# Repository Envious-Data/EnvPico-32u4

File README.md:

# EnvPico-32u4
Atmega32U4 board in the footprint of a Raspberry pi Pico, primarily inteded to be used for QMK

As you can imagine this is another kicad thing I just threw together on a whim but I did spend a bit more effort on this one and I might actually get this PCB made since I would like to get QMK properly running on my keyboards with VIA support.

Other than that it seems a bit easier to get Atmel chips over STM32s at the moment.

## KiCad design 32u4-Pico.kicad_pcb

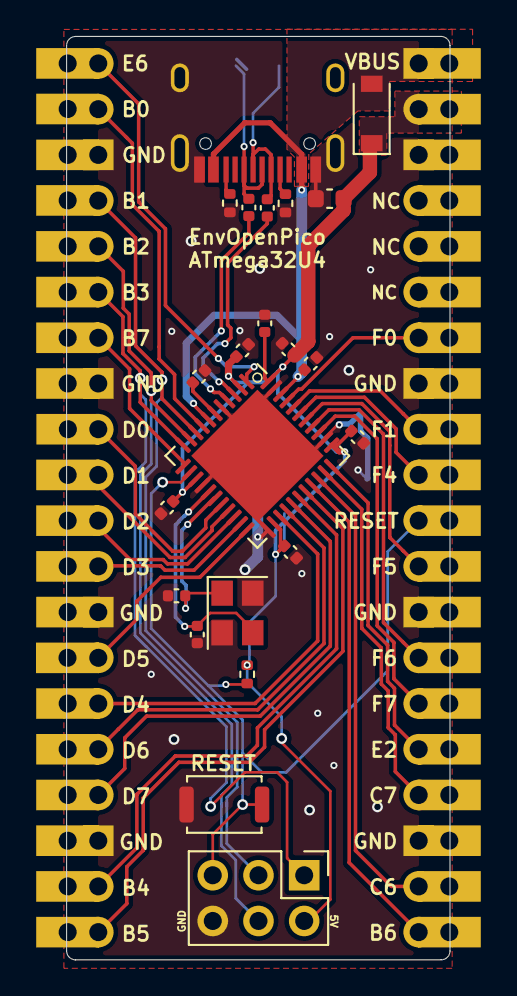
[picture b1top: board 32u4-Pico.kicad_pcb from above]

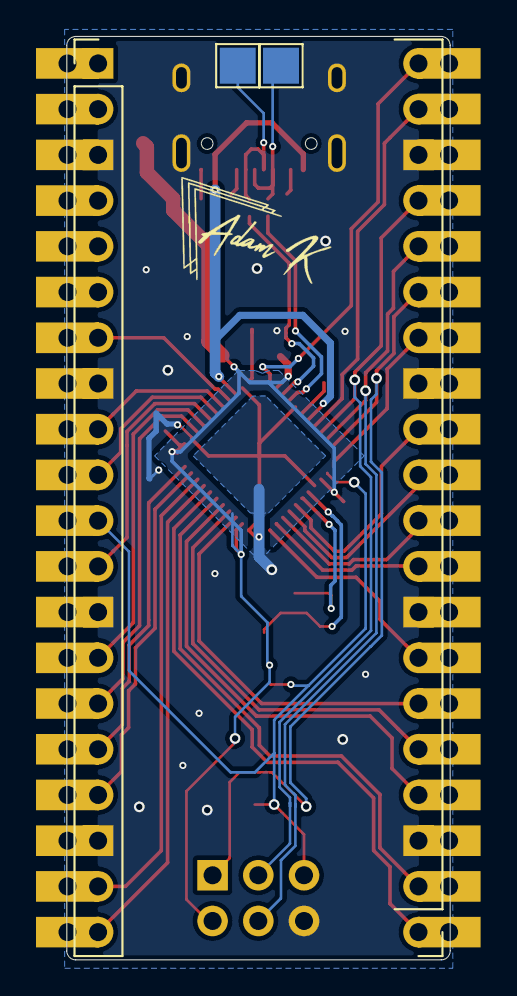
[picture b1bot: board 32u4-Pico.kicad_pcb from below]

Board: 2 copper layers, 21.3 x 51.3 mm, 26 parts (4 on the bottom side), 39 nets.

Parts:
C1: 10uf 0603 6.3V; C_0603_1608Metric
C2, C7: 22pF 0402; C_0402_1005Metric
C3, C10: 1uf 0402; C_0402_1005Metric
C4: 1uF 0402; C_0402_1005Metric
C5, C6, C8, C11, C13: 100nf 0402; C_0402_1005Metric
D1: 1n40002; D_SOD-123
ISP1: AVR-ISP-6; PinHeader_2x03_P2.54mm_Vertical
J3, J4: 2.54mm header 01x20; PinHeader_1x20_P2.54mm_Vertical
R1: 10K 0402; R_0402_1005Metric
R3, R4: 22Ohm 0402 Resistor; C_0402_1005Metric
R5, R6: 5.1K; R_0402_1005Metric
RSW1: SKRK; SW_Push_SPST_NO_Alps_SKRK
TP1, TP2: TestPoint; TestPoint_Pad_2.0x2.0mm
U1: ATmega32U4-MU; QFN-44-1EP_7x7mm_P0.5mm_EP5.2x5.2mm
USB1: TYPE-C-31-M-12; HRO-TYPE-C-31-M-12
Y1: 8MHz 3225_4p crystal; Crystal_SMD_3225-4Pin_3.2x2.5mm

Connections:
/GPIO0: J3.20, U1.1
/GPIO1: J3.19, U1.8
/GPIO5: J3.14, U1.12
/GPIO6: J3.12, U1.18
/GPIO7: J3.11, U1.19
/GPIO8: J3.10, U1.20
/GPIO9: J3.9, U1.21
/GPIO10: J3.7, U1.22
/GPIO11: J3.6, U1.25
/GPIO12: J3.5, U1.26
/GPIO13: J3.4, U1.27
/GPIO14: J3.2, U1.28
/GPIO15: J3.1, U1.29
/GPIO16: J4.20, U1.30
/GPIO17: J4.19, U1.31
/GPIO18: J4.17, U1.32
/GPIO19: J4.16, U1.33
/GPIO20: J4.15, U1.36
/GPIO21: J4.14, U1.37
/GPIO22: J4.12, U1.38
/GPIO26_ADC0: J4.10, U1.39
/GPIO27_ADC1: J4.9, U1.40
/GPIO28_ADC2: J4.7, U1.41
GND: C1.2, C2.1, C3.2, C4.2, C5.2, C6.2, C7.1, C8.2, C10.2, C11.2, C13.2, ISP1.6, J3.3, J3.8, J3.13, J3.18, J4.3, J4.8, J4.13, J4.18, R5.1, R6.1, RSW1.1, U1.5, U1.15, U1.23, U1.35, U1.43, U1.45, USB1.1, USB1.12, USB1.13, Y1.2, Y1.4
GPIO2-SCK: ISP1.3, J3.17, U1.9
GPIO3-mosi: ISP1.4, J3.16, U1.10
GPIO4-miso: ISP1.1, J3.15, U1.11
unnamed: C4.1, U1.6
unnamed: R3.2, U1.4
unnamed: R4.2, U1.3
unnamed: R5.2, USB1.4
unnamed: R6.2, USB1.10
RUN-RESET: ISP1.5, J4.11, R1.2, RSW1.2, U1.13
USB_D+: R3.1, TP1.1, USB1.6, USB1.8
USB_D-: R4.1, TP2.1, USB1.5, USB1.7
VBUS: C3.1, D1.2, J4.1, U1.7, U1.42, USB1.2, USB1.11
VSYS: C1.1, C5.1, C6.1, C8.1, C10.1, C11.1, C13.1, D1.1, ISP1.2, J4.2, R1.1, U1.2, U1.14, U1.24, U1.34, U1.44
XTAL1: C2.2, U1.17, Y1.1
XTAL2: C7.2, U1.16, Y1.3

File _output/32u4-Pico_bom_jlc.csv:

"Comment","Designator","Footprint","LCSC Part #"
"10uf 0603 6.3V","C1","C_0603_1608Metric","no_part_number"
"22pF 0402","C2,C7","C_0402_1005Metric","no_part_number"
"1uF 0402","C4","C_0402_1005Metric","no_part_number"
"100nf 0402","C8,C13,C11,C5,C6","C_0402_1005Metric","no_part_number"
"1uf 0402","C10,C3","C_0402_1005Metric","no_part_number"
"1n40002","D1","D_SOD-123","no_part_number"
"MountingHole","H1,H2,H3,H4","MountingHole_2.2mm_M2","no_part_number"
"AVR-ISP-6","ISP1","PinHeader_2x03_P2.54mm_Vertical","no_part_number"
"2.54mm header 01x20","J4,J3","PinHeader_1x20_P2.54mm_Vertical","no_part_number"
"10K 0402","R1","R_0402_1005Metric","no_part_number"
" 22Ohm  0402 Resistor","R3","C_0402_1005Metric","no_part_number"
"22Ohm 0402 Resistor","R4","C_0402_1005Metric","no_part_number"
"5.1K","R6,R5","R_0402_1005Metric","no_part_number"
"SKRK","RSW1","SW_Push_SPST_NO_Alps_SKRK","no_part_number"
"TestPoint","TP1,TP2","TestPoint_Pad_2.0x2.0mm","no_part_number"
"ATmega32U4-MU","U1","QFN-44-1EP_7x7mm_P0.5mm_EP5.2x5.2mm","no_part_number"
"TYPE-C-31-M-12","USB1","HRO-TYPE-C-31-M-12","no_part_number"
"8MHz 3225_4p crystal","Y1","Crystal_SMD_3225-4Pin_3.2x2.5mm","no_part_number"

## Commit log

2021-08-06 Inidial Commit +1
2021-08-06 implemented Rest pin in place of RUN and added a reset button + a couple other bits
2021-08-14 more via fixes and all.
2021-08-15 Added keepout zones near the pin holes and corrected all errors as per DRC.
2021-08-17 swapped oscillator for crystal because easier to get a hold of as of right now. (and a bit of tidying up)
2021-08-30 small adjustment fix for the vbus/vsys diode.
2021-09-10 Added ISP header in schematic.
2021-09-10 added ISP header on board and routed traces for it.
2021-09-13 fixed a few silkscreen bits, i.e 3.3V to NC
2021-09-16 Generated updated gerber and stuff
2021-12-30 added correct orientation USB TP Pads to match RPI PICO and my Pico clone
2021-12-30 generated updated gerber
2021-12-30 forgot to exclude BOM and CPL from gitignore
2022-02-18 updated git ignore
2022-11-25 smol fix-y
2022-11-25 change some egregious design choices
